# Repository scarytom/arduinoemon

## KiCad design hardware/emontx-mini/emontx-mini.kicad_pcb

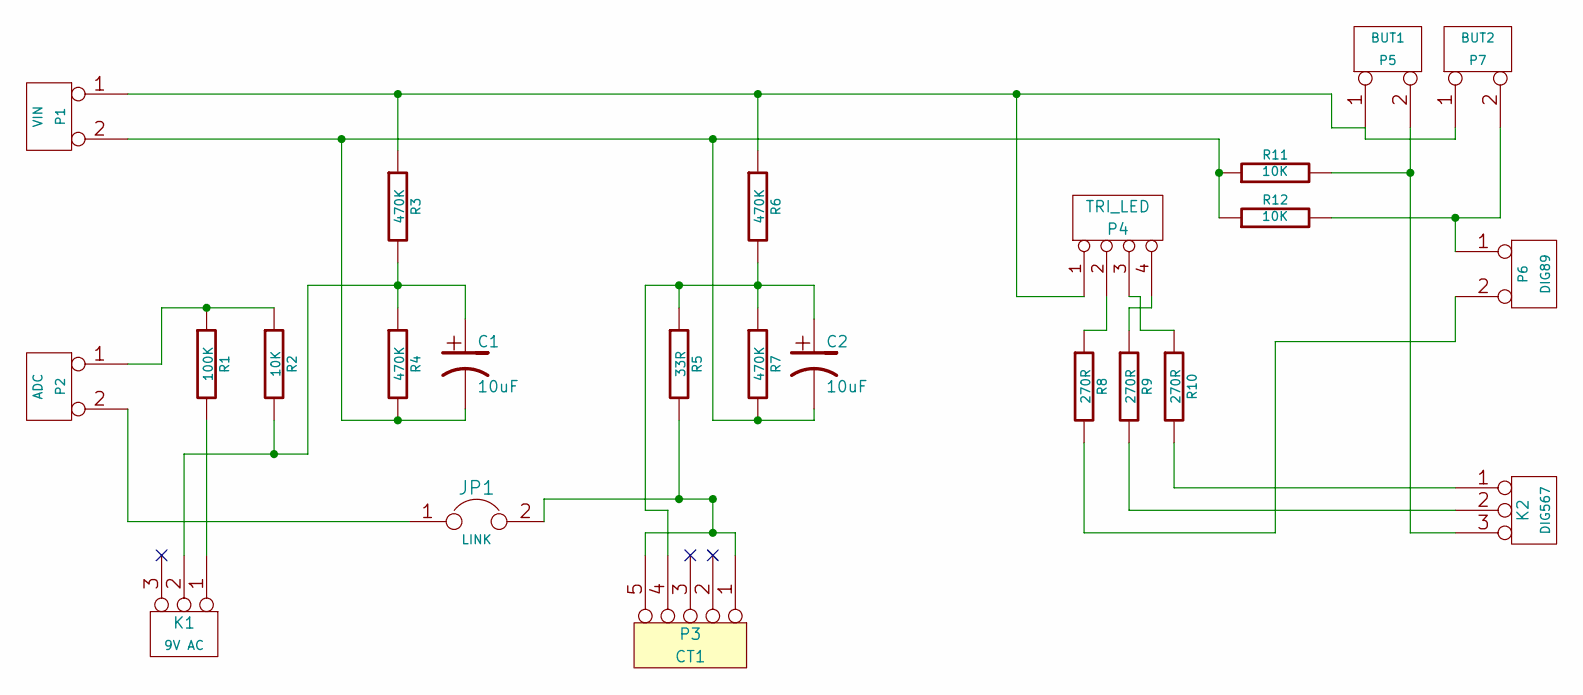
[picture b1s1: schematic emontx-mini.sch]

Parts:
C1, C2: 10uF
JP1: LINK
K1: 9V AC
K2: DIG567
P1: VIN
P2: ADC
P3: CT1
P4: TRI_LED
P5: BUT1
P6: DIG89
P7: BUT2
R1: 100K
R2, R11, R12: 10K
R3, R4, R6, R7: 470K
R5: 33R
R8, R9, R10: 270R

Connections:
unnamed: K2.1, R10.2
unnamed: K2.2 (PM), R9.2
unnamed: JP1.2, P3.1, P3.5, R5.2
unnamed: C2.1, P3.4, R5.1, R6.2, R7.1
unnamed: P6.1, P7.2 (PM), R12.2
unnamed: JP1.1, P2.2 (PM)
unnamed: P6.2 (PM), R8.2
unnamed: K2.3, P5.2 (PM), R11.2
unnamed: P4.2, R8.1
unnamed: P4.3, R10.1
unnamed: P4.4, R9.1
unnamed: K1.1, R1.2
unnamed: C1.1, K1.2 (PM), R2.2, R3.2, R4.1
unnamed: P2.1, R1.1, R2.1
unnamed: P1.1, P4.1, P5.1, P7.1, R3.1, R6.1
unnamed: C1.2, C2.2, P1.2 (PM), R4.2, R7.2, R11.1, R12.1

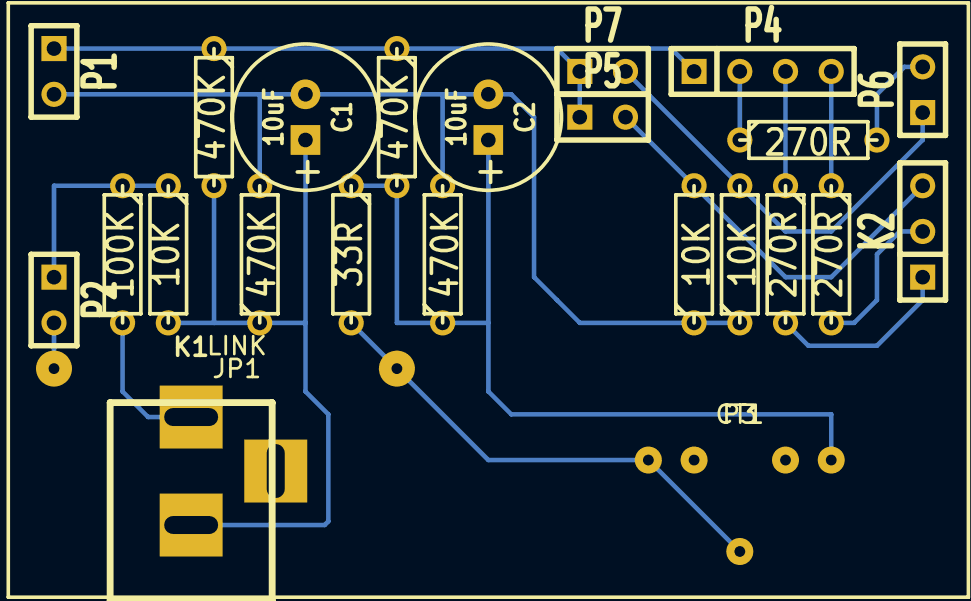
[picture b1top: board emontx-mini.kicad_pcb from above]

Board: 2 copper layers, 24 parts (0 on the bottom side), 16 nets.
